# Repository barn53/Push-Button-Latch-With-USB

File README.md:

# Push Button Latch With USB

A Push Button Latch circuit with MOSFETs
Vishai SIA527DJ-T1-GE3

With digital off signal

Powered by Micro-USB, output 3.3V and 5V.

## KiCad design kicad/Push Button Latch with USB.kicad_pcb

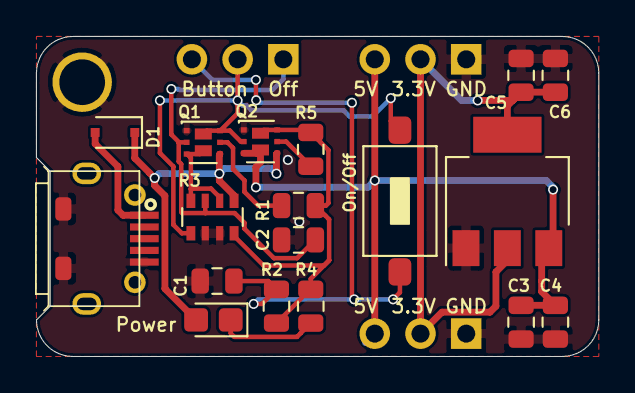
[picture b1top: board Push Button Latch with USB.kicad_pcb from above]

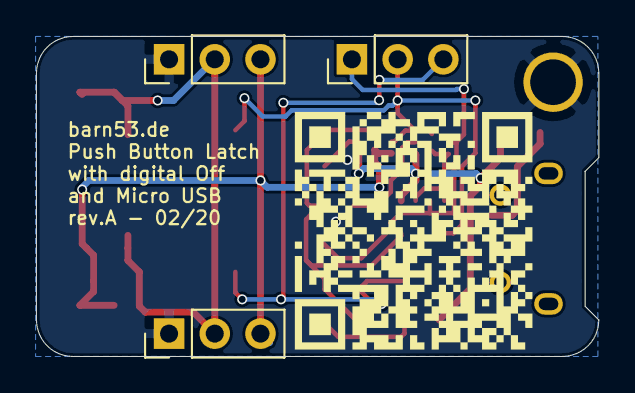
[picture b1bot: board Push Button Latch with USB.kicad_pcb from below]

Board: 2 copper layers, 31.2 x 17.8 mm, 22 parts (4 on the bottom side), 13 nets.

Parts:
C1: 330n; C_0805_2012Metric
C2, C3, C5: 100n; C_0805_2012Metric
C4, C6: 10u; C_0805_2012Metric
D1: BAT60A; D_SOD-323F
D2: Power; LED_0805_2012Metric_Castellated
J1: USB_B_Micro; MicroUSB_through_hole_fixing
J2, J3, J4: Conn_01x03; PinHeader_1x03_P2.54mm_Vertical
Q1, Q2: SIA527DJ-T1-GE3; PowerPAK_SC70-6L_Dual
QR*****: barn53
R1, R5: 100k; R_0805_2012Metric
R2: 1M; R_0805_2012Metric
R3: 10k; R_Array_Convex_4x0603
R4: 470; R_0805_2012Metric
SW1: On/Off; SMD_Push_Button
U1: AMS1117-3.3; SOT-223-3_TabPin2

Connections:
/+3V3: C5.1, C6.1, J3.2, J4.2, U1.2
/Bt1: C1.1, J2.3, R2.2, SW1.1
/Bt2: J2.2, Q1.6, Q2.2, R3.1, SW1.2
/Off: C2.1, J2.1, Q1.2, R3.7
/VBus: D1.2, J1.1
/VIn: D1.1, D2.2, Q1.4, Q2.4, R3.5
/VOut: C3.1, C4.1, J3.3, J4.3, Q2.3, U1.3
GND: C1.2, C2.2, C3.2, C4.2, C5.2, C6.2, J1.5, J1.6, J3.1, J4.1, Q1.1, Q2.1, R3.2, R3.3, U1.1
unnamed: D2.1, R4.1
unnamed: Q1.3, R3.6, R3.8
unnamed: Q1.5, R1.1
unnamed: Q2.5, R5.1
unnamed: Q2.6, R1.2, R2.1, R3.4, R4.2, R5.2

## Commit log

2020-01-15 first steps
2020-01-22 Seems like rev.A is finished
